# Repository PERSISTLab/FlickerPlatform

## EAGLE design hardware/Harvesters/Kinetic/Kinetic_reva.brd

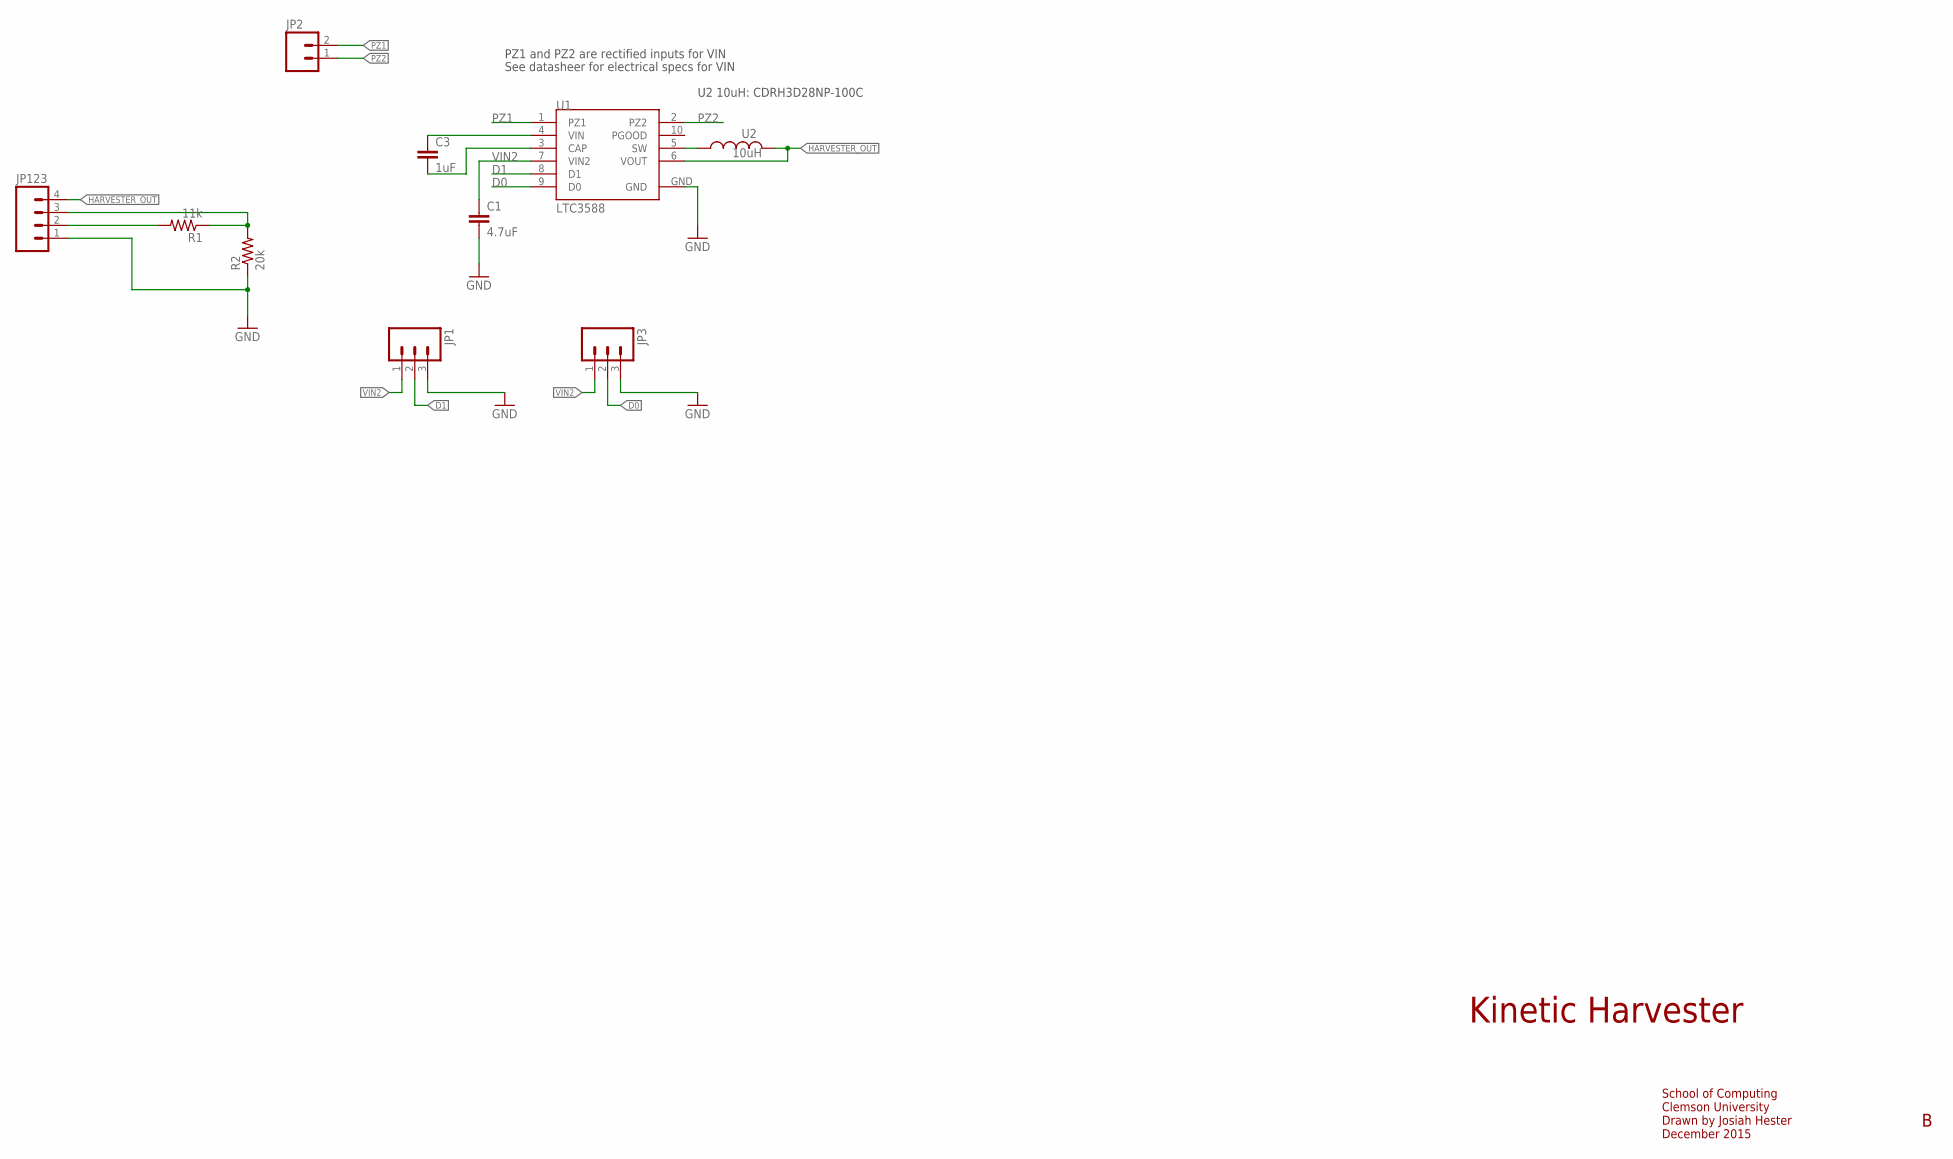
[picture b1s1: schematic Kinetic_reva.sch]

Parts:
C1: 4.7uF; 0402-CAP; MPN C1005X5R1A475M050BC
C3: 1uF; 0402-CAP; MPN 0402ZD105KAT2A
JP1, JP3: M03; 1X03-1.27MM; MPN GRPB031VWVN-RC
JP2: M02LOCK; 1X02_LOCK
JP123: M041.27MM; 1X04-1.27MM; MPN GRPB041VWVN-RC
R1: 11k; 0603; MPN RC0603JR-0711KL
R2: 20k; 0603; MPN CRCW060320K0FKEA
U1: LTC3588; MSOP-10-GNDPAD; MPN LTC3588EMSE-1#PBF; DIGIKEY LTC3588EMSE-1#PBF-ND
U2: 10uH; CDRH3D28; MPN CDRH3D16NP-100NC; DIGIKEY 308-2298-1-ND

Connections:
D0: JP3.2, U1.9 (D0)
D1: JP1.2, U1.8 (D1)
GND: C1.2, JP1.3, JP3.3, JP123.1, R2.1, U1.GND
HARVESTER_OUT: JP123.4, U1.6 (VOUT), U2.2
unnamed: JP123.3, R1.1, R2.2
unnamed: JP123.2, R1.2
unnamed: C3.2, U1.3 (CAP)
unnamed: U1.5 (SW), U2.1
PZ1: JP2.2, U1.1 (PZ1)
PZ2: JP2.1, U1.2 (PZ2)
VIN: C3.1, U1.4 (VIN)
VIN2: C1.1, JP1.1, JP3.1, U1.7 (VIN2)

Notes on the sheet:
Kinetic Harvester
School of Computing Clemson University Drawn by Josiah Hester December 2015
U2 10uH: CDRH3D28NP-100C
PZ1 and PZ2 are rectified inputs for VIN
See datasheer for electrical specs for VIN

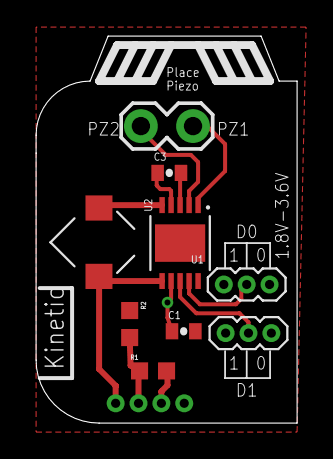
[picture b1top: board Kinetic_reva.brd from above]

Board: 2 copper layers, 14.5 x 21.5 mm, 10 parts (1 on the bottom side), 12 nets.

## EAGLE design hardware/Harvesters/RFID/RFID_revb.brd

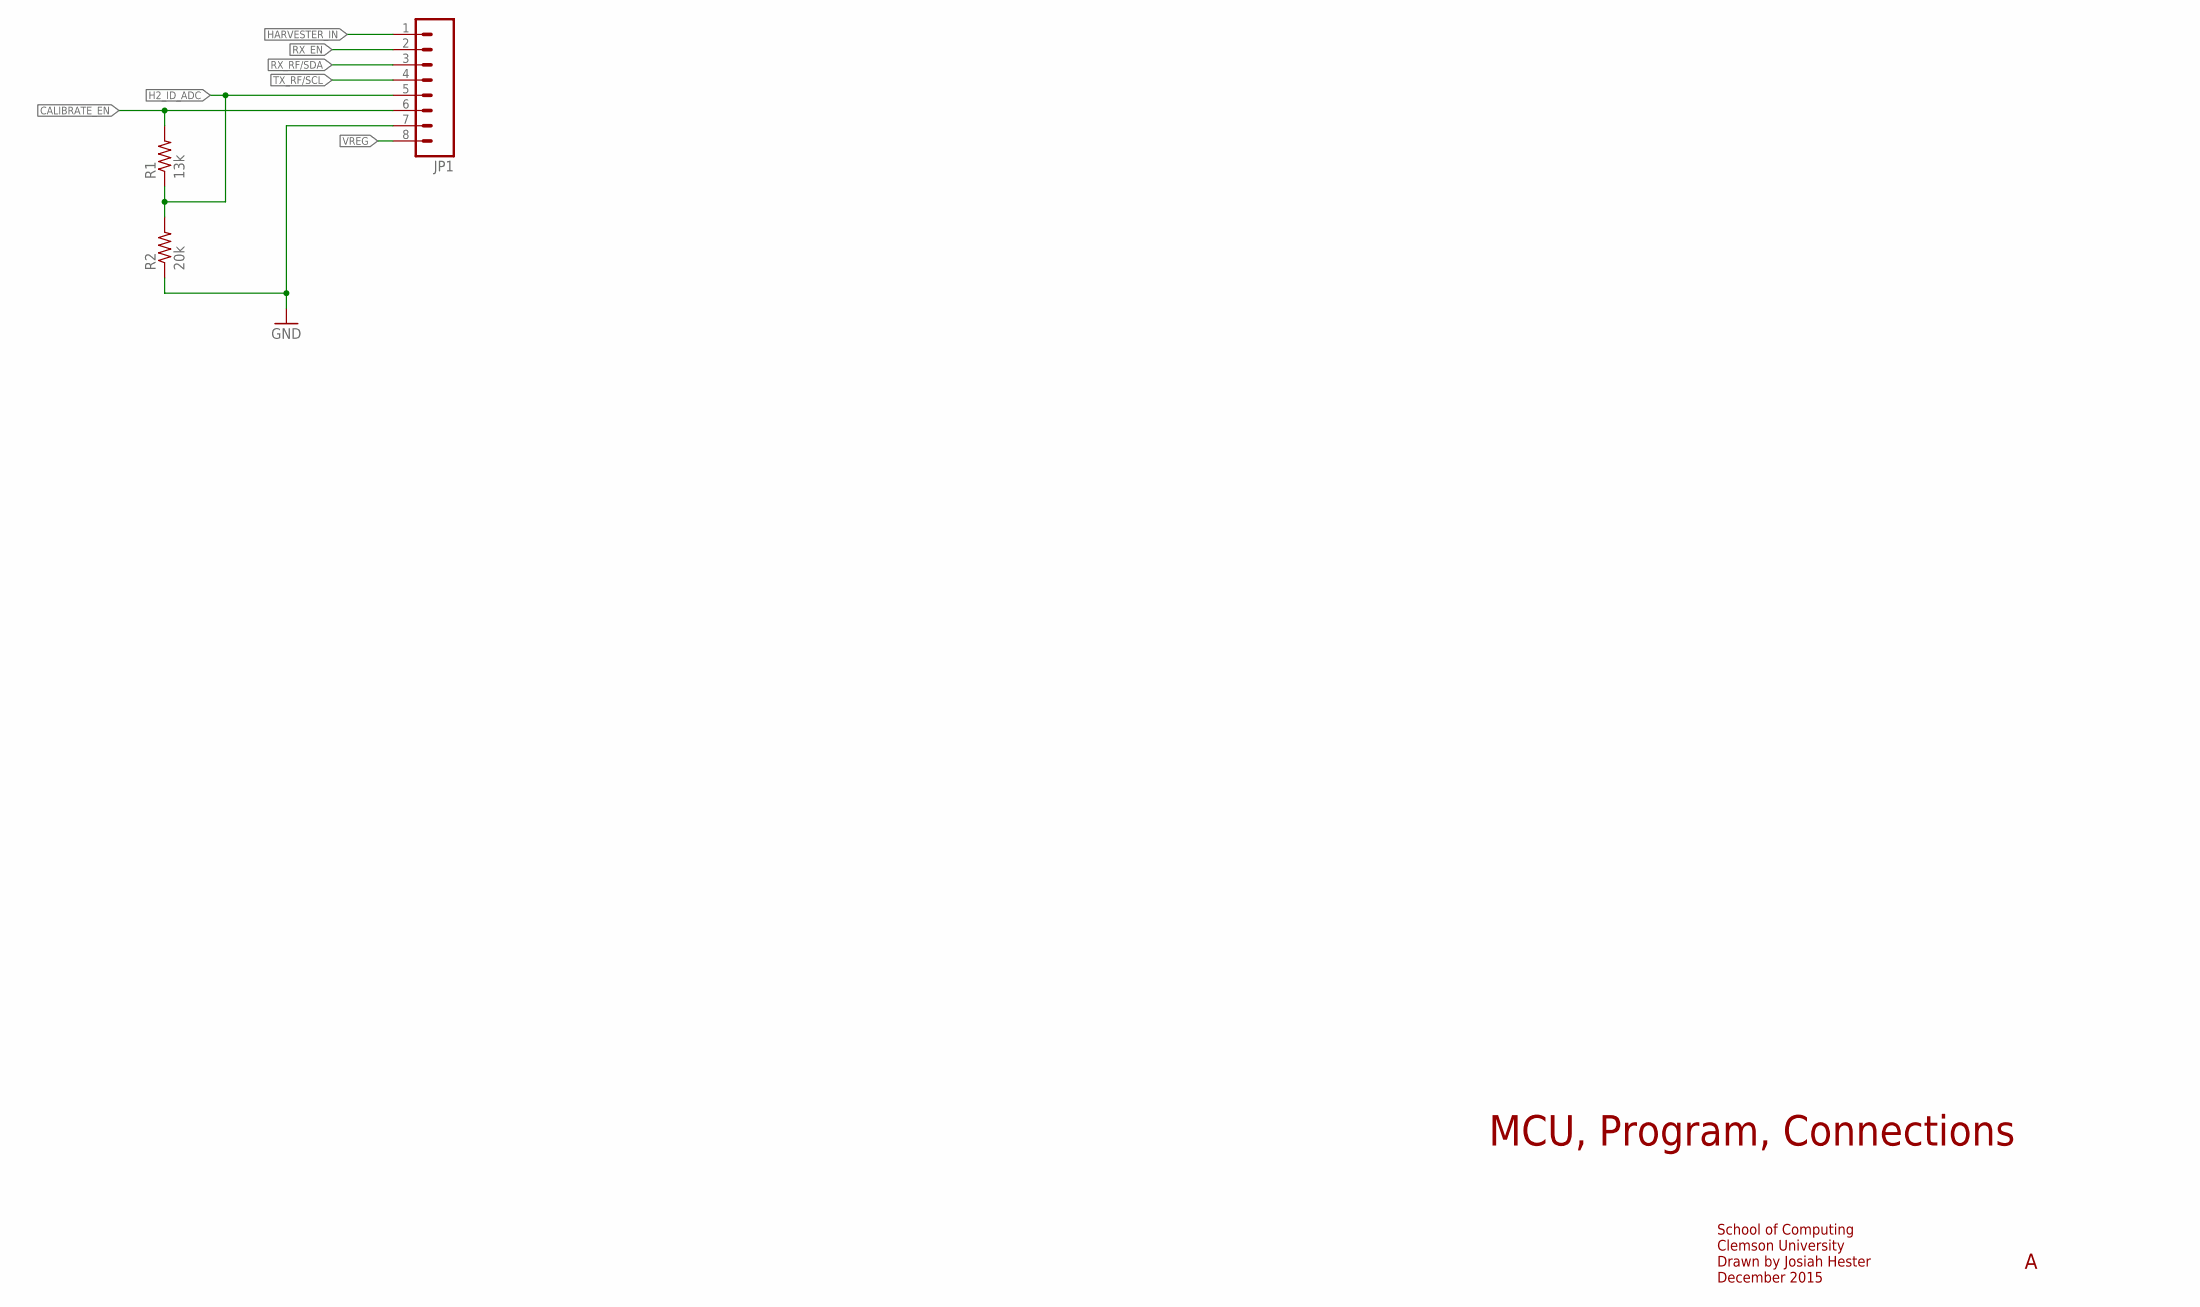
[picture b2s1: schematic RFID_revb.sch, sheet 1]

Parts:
JP1: M081.27MM; 1X08-1.27MM; MPN GRPB081VWVN-RC
R1: 13k; 0603; MPN RC0603FR-0713KL
R2: 20k; 0603; MPN CRCW060320K0FKEA

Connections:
CALIBRATE_EN: JP1.6, R1.2
GND: JP1.7, R2.1; also elsewhere on the board
H2_ID_ADC: JP1.5, R1.1, R2.2
HARVESTER_IN: JP1.1; also elsewhere on the board
RX_EN: JP1.2; also elsewhere on the board
RX_RF/SDA: JP1.3; also elsewhere on the board
TX_RF/SCL: JP1.4; also elsewhere on the board
VREG: JP1.8; also elsewhere on the board

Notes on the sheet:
MCU, Program, Connections
School of Computing Clemson University Drawn by Josiah Hester December 2015

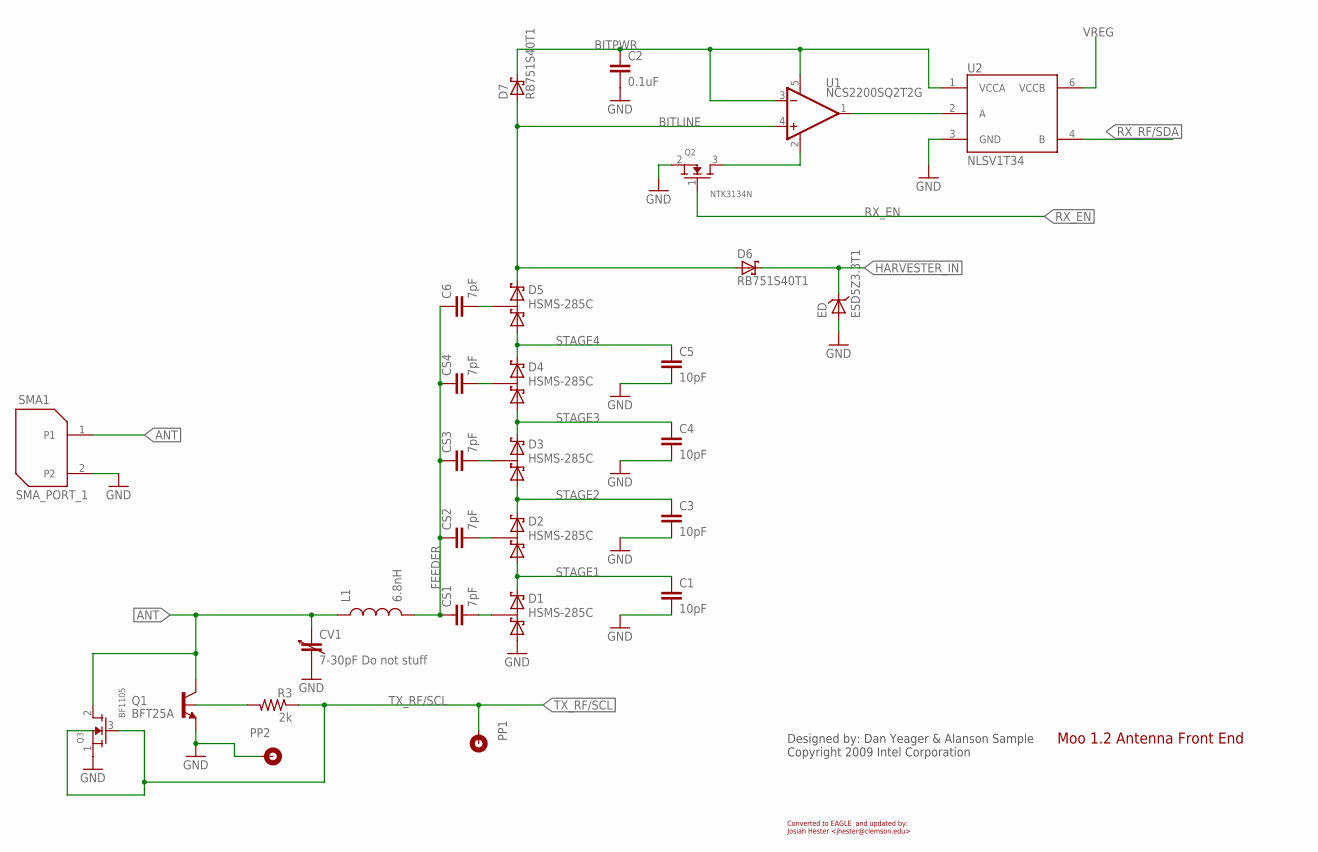
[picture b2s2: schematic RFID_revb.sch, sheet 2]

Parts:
C1, C3, C4, C5: 10pF; 0402; MPN GRM1555C1H100JA01D
C2: 0.1uF; 0402; MPN 0402YD104KAT2A
C6: 7pF; 0402; MPN GRM1555C1H7R0DA01D
CS1, CS2, CS3: 7pF; 0402; MPN GRM1555C1H7R0DA01D; DIGIKEY 490-5878-1-ND
CS4: 7pF; 0402; MPN GRM1555C1H7R0DA01D
CV1: 7-30pF Do not stuff; VAR-CAP_603_1PRIMARY; MPN TZY2R250AC01R00
D1, D2, D3, D4, D5: HSMS-285C; SOT-323,_HSMS-285C_1PRIMARY; MPN HSMS-285C-BLKG
D6, D7: RB751S40T1; SOD-523_1PRIMARY; MPN RB751S40T1G
ED: ESD5Z3.3T1; SOD-523_1PRIMARY; MPN ESD5Z3.3T1G
L1: 6.8nH; 0603_1PRIMARY; MPN MLG1608B6N8DT000
PP1: PROBE_POINT_2; PROBE_POINT_2PRIMARY
PP2: PROBE_POINT_1; PROBE_POINT_2PRIMARY
Q1: BFT25A; SOT-23_1PRIMARY; MPN BFT25A,215; DIGIKEY 568-1992-1-ND
Q2: NTK3134N; SOT723_1PRIMARY; MPN NTK3134NT1G
Q3: BF1105; SOT-143R; MPN BF1105R,215
R3: 2k; 0402; MPN CRCW04022K00FKED
SMA1: SMA_PORT_1; SMA_PORT_1PRIMARY
U1: NCS2200SQ2T2G; SC70-5_1PRIMARY; MPN NCS2200SQ2T2G; DIGIKEY NCS2200SQ2T2GOSCT-ND
U2: NLSV1T34; ULLGA6; MPN NLSV1T34AMX1TCG

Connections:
ANT: CV1.1, L1.1, Q1.3 (C), Q3.2 (D), SMA1.1
BITLINE: D5.2, D6.2 (A), D7.2 (A), U1.4
BITPWR: C2.1, D7.1 (C), U1.3, U1.5, U2.1 (VCCA)
CONTROL: Q1.1 (B), R3.2
FEEDER: C6.1, CS1.1, CS2.1, CS3.1, CS4.1, L1.2
GND: C1.2, C2.2, C3.2, C4.2, C5.2, CV1.2, D1.1, ED.2, PP2.1, Q1.2 (E), Q2.2, Q3.1 (S), SMA1.2, U2.3 (GND); also elsewhere on the board
HARVESTER_IN: D6.1 (C), ED.1; also elsewhere on the board
unnamed: U1.1, U2.2 (A)
unnamed: Q2.3, U1.2
NETCS1_2: CS1.2, D1.3
NETCS2_2: CS2.2, D2.3
NETCS3_2: CS3.2, D3.3
NETCS4_2: CS4.2, D4.3
NETCS5_2: C6.2, D5.3
RX_EN: Q2.1; also elsewhere on the board
RX_RF/SDA: U2.4 (B); also elsewhere on the board
STAGE1: C1.1, D1.2, D2.1
STAGE2: C3.1, D2.2, D3.1
STAGE3: C4.1, D3.2, D4.1
STAGE4: C5.1, D4.2, D5.1
TX_RF/SCL: PP1.1, Q3.3 (G), Q3.4 (G2), R3.1; also elsewhere on the board
VREG: U2.6 (VCCB); also elsewhere on the board

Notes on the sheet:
Designed by: Dan Yeager & Alanson Sample Copyright 2009 Intel Corporation
Moo 1.2 Antenna Front End
Converted to EAGLE and updated by: Josiah Hester <jhester@clemson.edu>

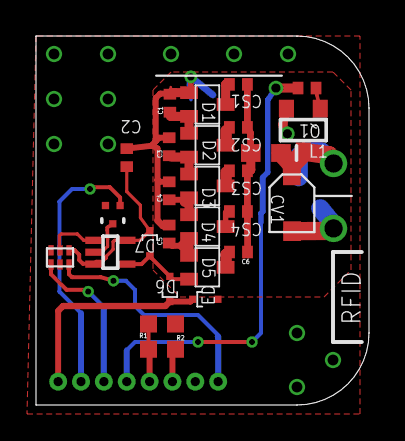
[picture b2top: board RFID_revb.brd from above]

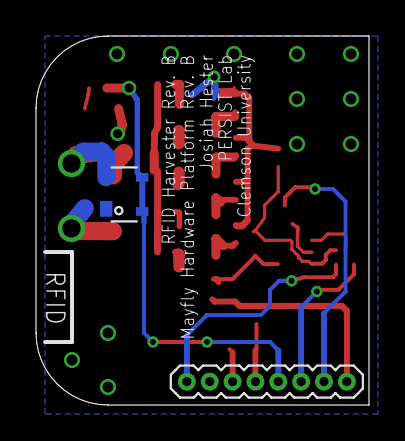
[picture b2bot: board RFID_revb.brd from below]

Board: 2 copper layers, 18.5 x 20.5 mm, 32 parts (2 on the bottom side), 24 nets.

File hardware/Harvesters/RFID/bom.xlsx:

Part | Value | Device | Package | Description | DIGIKEY | MPN
C1 | 10pF | C-EU | 402 |  |  | GRM1555C1H100JA01D
C2 | 0.1uF | C-EU | 402 |  |  | 0402YD104KAT2A
C3 | 10pF | C-EU | 402 |  |  | GRM1555C1H100JA01D
C4 | 10pF | C-EU | 402 |  |  | GRM1555C1H100JA01D
C5 | 10pF | C-EU | 402 |  |  | GRM1555C1H100JA01D
C6 | 7pF | C-EU | 402 |  |  | GRM1555C1H7R0DA01D
CS1 | 7pF | C-EU | 402 |  | 490-5878-1-ND | GRM1555C1H7R0DA01D
CS2 | 7pF | C-EU | 402 |  | 490-5878-1-ND | GRM1555C1H7R0DA01D
CS3 | 7pF | C-EU | 402 |  | 490-5878-1-ND | GRM1555C1H7R0DA01D
CS4 | 7pF | C-EU | 402 |  |  | GRM1555C1H7R0DA01D
CV1 | 7-30pF Do not stuff | VAR-CAP_603_1 | VAR-CAP_603_1PRIMARY |  |  | TZY2R250AC01R00
D1 | HSMS-285C | HSMS-285C | SOT-323,_HSMS-285C_1PRIMARY |  |  | HSMS-285C-BLKG
D2 | HSMS-285C | HSMS-285C | SOT-323,_HSMS-285C_1PRIMARY |  |  | HSMS-285C-BLKG
D3 | HSMS-285C | HSMS-285C | SOT-323,_HSMS-285C_1PRIMARY |  |  | HSMS-285C-BLKG
D4 | HSMS-285C | HSMS-285C | SOT-323,_HSMS-285C_1PRIMARY |  |  | HSMS-285C-BLKG
D5 | HSMS-285C | HSMS-285C | SOT-323,_HSMS-285C_1PRIMARY |  |  | HSMS-285C-BLKG
D6 | RB751S40T1 | RB751S40T1 | SOD-523_1PRIMARY |  |  | RB751S40T1G
D7 | RB751S40T1 | RB751S40T1 | SOD-523_1PRIMARY |  |  | RB751S40T1G
ED | ESD5Z3.3T1 | ESD5Z3.3T1 | SOD-523_1PRIMARY |  |  | ESD5Z3.3T1G
JP1 |  | M081.27MM | 1X08-1.27MM | Header 8 |  | GRPB081VWVN-RC
L1 | 6.8nH | 0603_1 | 0603_1PRIMARY |  |  | MLG1608B6N8DT000
PP1 | PROBE_POINT_2 | PROBE_POINT_2 | PROBE_POINT_2PRIMARY
PP2 | PROBE_POINT_1 | PROBE_POINT_1 | PROBE_POINT_2PRIMARY
Q1 | BFT25A | BFT25A | SOT-23_1PRIMARY |  | 568-1992-1-ND | BFT25A,215
Q2 | NTK3134N | NTK3134N | SOT723_1PRIMARY |  |  | NTK3134NT1G
Q3 | BF1105 | BF1105 | SOT-143R |  |  | BF1105R,215
R1 | 13k | R-EU0603 | 603 |  |  | RC0603FR-0713KL
R2 | 20k | R-EU0603 | 603 |  |  | CRCW060320K0FKEA
R3 | 2k | R-EU | 402 |  |  | CRCW04022K00FKED
SMA1 | SMA_PORT_1 | SMA_PORT_1 | SMA_PORT_1PRIMARY
U1 | NCS2200SQ2T2G | NCS2200SQ2T2G | SC70-5_1PRIMARY |  |  | 0402YD104KAT2A
U2 | NLSV1T34 | NLSV1T34 | ULLGA6 |  |  | NLSV1T34AMX1TCG

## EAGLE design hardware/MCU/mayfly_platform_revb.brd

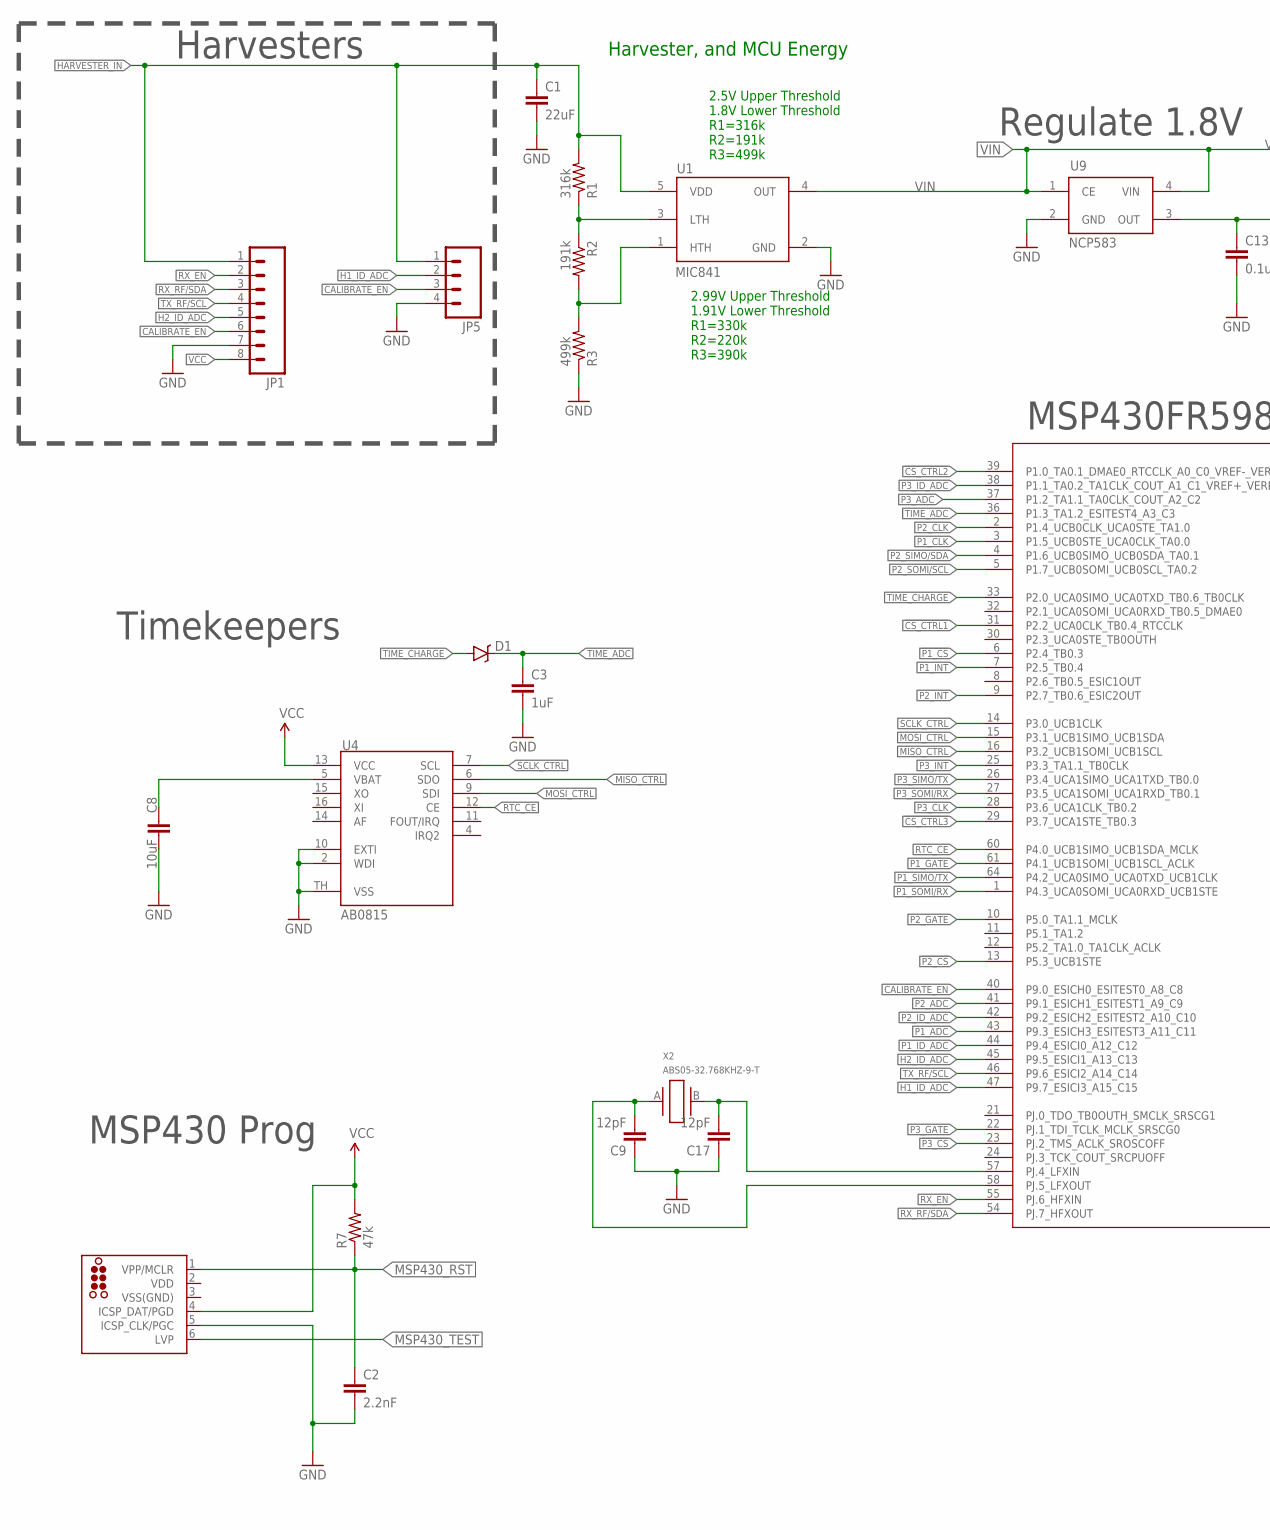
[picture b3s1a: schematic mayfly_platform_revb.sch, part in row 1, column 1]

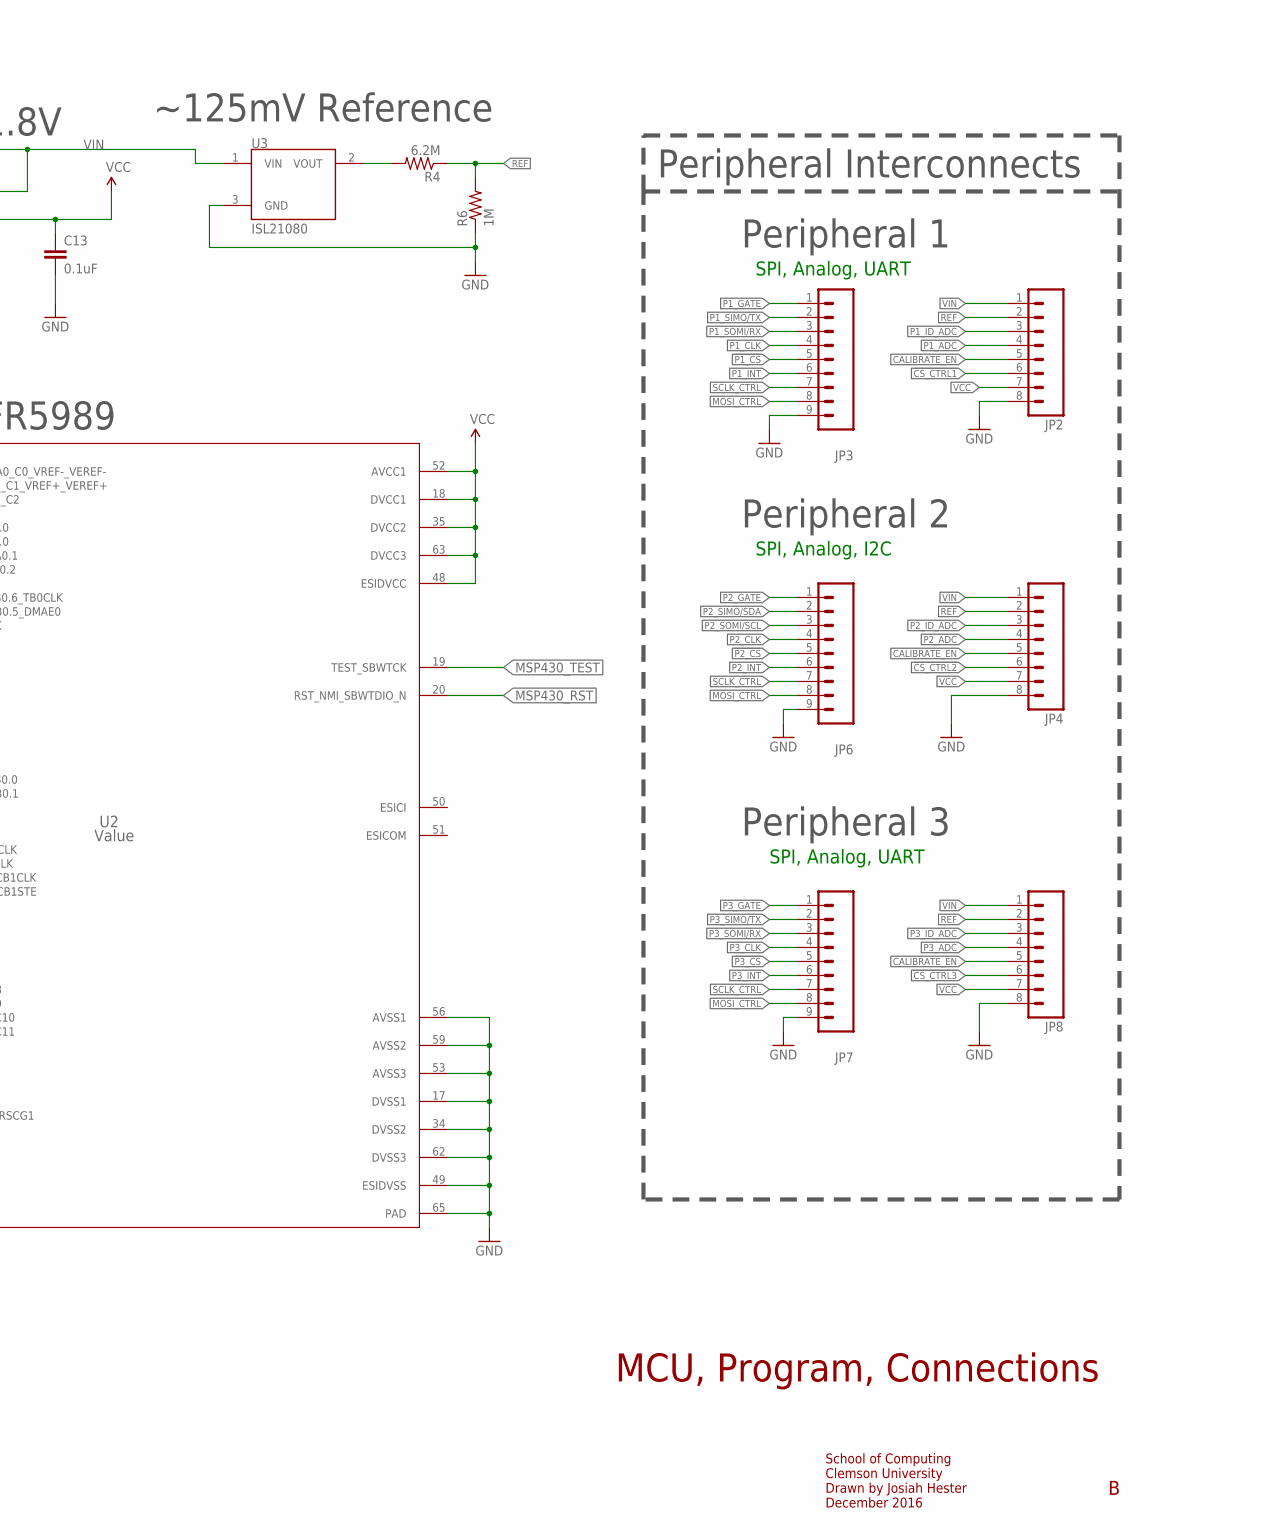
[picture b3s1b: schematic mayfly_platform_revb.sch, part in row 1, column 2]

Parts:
C1: 22uF; 1210; MANUFACTURERPARTNUMBER CL32A226KAJNNNE
C2: 2.2nF; 0603; MPN 06035C222KAT2A
C3: 1uF; 0603; MANUFACTURERPARTNUMBER 0603YD105KAT2A
C8: 10uF; 0805; MPN 0805YD106KAT2A
C9, C17: 12pF; 0603; MPN CL10C120JB8NNNC
C13: 0.1uF; 0603; MANUFACTURERPARTNUMBER 0603YC104KAT2A
D1: RB751; SOD-523; MPN BAS40-02V-V-G-08; DIGIKEY BAS40-02V-V-G-08GICT-ND
J1: TC2030-MCP-NL
JP1: M081.27MM; 1X08-1.27MM; MANUFACTURERPARTNUMBER 851-43-008-10-001000; DIGIKEY ED90570-ND
JP2, JP4, JP8: M081.27MM; 1X08-1.27MM; MPN 851-43-008-10-001000; DIGIKEY ED90570-ND
JP3, JP6, JP7: M091.27MM; 1X09-1.27MM; MPN 851-87-009-10-001101; DIGIKEY 1212-1354-ND
JP5: M041.27MM; 1X04-1.27MM; MANUFACTURERPARTNUMBER 851-43-004-10-001000; DIGIKEY ED90528-ND
R1: 316k; 0603; MANUFACTURERPARTNUMBER RC0603FR-07316KL; DIGIKEY 311-316KHRCT-ND
R2: 191k; 0603; MANUFACTURERPARTNUMBER RC0603FR-07191KL; DIGIKEY 311-191KHRCT-ND
R3: 499k; 0603; MANUFACTURERPARTNUMBER RC0603FR-07499KL; DIGIKEY 311-499KHRCT-ND
R4: 6.2M; 0603; MPN CRCW06036M20FKEA; DIGIKEY 541-6.20MHCT-ND
R6: 1M; 0603; MPN RC0603FR-071ML; DIGIKEY 311-1.00MHRCT-ND
R7: 47k; 0603; MPN CRCW060347K0JNEA
U1: MIC841; SC70-5; MPN MIC841HYC5-TR; DIGIKEY 576-2923-1-ND
U2: Value; RGC0064B; MPN MSP430FR59891IRGCT; DIGIKEY 296-42031-1-ND
U3: ISL21080; SOT-23; MPN ISL21080DIH309Z-TK; DIGIKEY ISL21080DIH309Z-TKCT-ND
U4: AB0815; QFN16; MPN AB0815-T3
U9: NCP583; SC82-AB_1PRIMARY; MPN NCP583SQ18T1G; DIGIKEY NCP583SQ18T1GOSCT-ND
X2: ABS05-32.768KHZ-9-T; ABS05; MPN ABS05-32.768KHZ-9-T

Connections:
!CS_CTRL1: JP2.6, U2.31 (P2.2_UCA0CLK_TB0.4_RTCCLK)
!CS_CTRL2: JP4.6, U2.39 (P1.0_TA0.1_DMAE0_RTCCLK_A0_C0_VREF-_VER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)
!CS_CTRL3: JP8.6, U2.29 (P3.7_UCA1STE_TB0.3)
!P1_CS: JP3.5, U2.6 (P2.4_TB0.3)
!P2_CS: JP6.5, U2.13 (P5.3_UCB1STE)
!P3_CS: JP7.5, U2.23 (PJ.2_TMS_ACLK_SROSCOFF)
CALIBRATE_EN: JP1.6, JP2.5, JP4.5, JP5.3, JP8.5, U2.40 (P9.0_ESICH0_ESITEST0_A8_C8)
GND: C1.2, C2.2, C3.2, C8.2, C9.1, C13.2, C17.1, J1.5 (ICSP_CLK/PGC), JP1.7, JP2.8, JP3.9, JP4.8, JP5.4, JP6.9, JP7.9, JP8.8, R3.1, R6.1, U1.2 (GND), U2.17 (DVSS1), U2.34 (DVSS2), U2.49 (ESIDVSS), U2.53 (AVSS3), U2.56 (AVSS1), U2.59 (AVSS2), U2.62 (DVSS3), U2.65 (PAD), U3.3 (GND), U4.2 (WDI), U4.10 (EXTI), U4.TH (VSS), U9.2 (GND)
H1_ID_ADC: JP5.2, U2.47 (P9.7_ESICI3_A15_C15)
H2_ID_ADC: JP1.5, U2.45 (P9.5_ESICI1_A13_C13)
HARVESTER_IN: C1.1, JP1.1, JP5.1, R1.2, U1.5 (VDD)
MISO_CTRL: U2.16 (P3.2_UCB1SOMI_UCB1SCL), U4.6 (SDO)
MOSI_CTRL: JP3.8, JP6.8, JP7.8, U2.15 (P3.1_UCB1SIMO_UCB1SDA), U4.9 (SDI)
MSP430_RST: C2.1, J1.1 (VPP/MCLR), R7.1, U2.20 (RST_NMI_SBWTDIO_N)
MSP430_TEST: J1.6 (LVP), U2.19 (TEST_SBWTCK)
unnamed: R1.1, R2.1, U1.3 (LTH)
unnamed: R4.2, U3.2 (VOUT)
unnamed: R2.2, R3.2, U1.1 (HTH)
unnamed: C17.2, U2.57 (PJ.4_LFXIN), X2.B (2)
unnamed: C9.2, U2.58 (PJ.5_LFXOUT), X2.A (1)
unnamed: C8.1, U4.5 (VBAT)
P1_ADC: JP2.4, U2.43 (P9.3_ESICH3_ESITEST3_A11_C11)
P1_CLK: JP3.4, U2.3 (P1.5_UCB0STE_UCA0CLK_TA0.0)
P1_GATE: JP3.1, U2.61 (P4.1_UCB1SOMI_UCB1SCL_ACLK)
P1_ID_ADC: JP2.3, U2.44 (P9.4_ESICI0_A12_C12)
P1_INT: JP3.6, U2.7 (P2.5_TB0.4)
P1_SIMO/TX: JP3.2, U2.64 (P4.2_UCA0SIMO_UCA0TXD_UCB1CLK)
P1_SOMI/RX: JP3.3, U2.1 (P4.3_UCA0SOMI_UCA0RXD_UCB1STE)
P2_ADC: JP4.4, U2.41 (P9.1_ESICH1_ESITEST1_A9_C9)
P2_CLK: JP6.4, U2.2 (P1.4_UCB0CLK_UCA0STE_TA1.0)
P2_GATE: JP6.1, U2.10 (P5.0_TA1.1_MCLK)
P2_ID_ADC: JP4.3, U2.42 (P9.2_ESICH2_ESITEST2_A10_C10)
P2_INT: JP6.6, U2.9 (P2.7_TB0.6_ESIC2OUT)
P2_SIMO/SDA: JP6.2, U2.4 (P1.6_UCB0SIMO_UCB0SDA_TA0.1)
P2_SOMI/SCL: JP6.3, U2.5 (P1.7_UCB0SOMI_UCB0SCL_TA0.2)
P3_ADC: JP8.4, U2.37 (P1.2_TA1.1_TA0CLK_COUT_A2_C2)
P3_CLK: JP7.4, U2.28 (P3.6_UCA1CLK_TB0.2)
P3_GATE: JP7.1, U2.22 (PJ.1_TDI_TCLK_MCLK_SRSCG0)
P3_ID_ADC: JP8.3, U2.38 (P1.1_TA0.2_TA1CLK_COUT_A1_C1_VREF+_VERE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)
P3_INT: JP7.6, U2.25 (P3.3_TA1.1_TB0CLK)
P3_SIMO/TX: JP7.2, U2.26 (P3.4_UCA1SIMO_UCA1TXD_TB0.0)
P3_SOMI/RX: JP7.3, U2.27 (P3.5_UCA1SOMI_UCA1RXD_TB0.1)
REF: JP2.2, JP4.2, JP8.2, R4.1, R6.2
RTC_CE: U2.60 (P4.0_UCB1SIMO_UCB1SDA_MCLK), U4.12 (CE)
RX_EN: JP1.2, U2.55 (PJ.6_HFXIN)
RX_RF/SDA: JP1.3, U2.54 (PJ.7_HFXOUT)
SCLK_CTRL: JP3.7, JP6.7, JP7.7, U2.14 (P3.0_UCB1CLK), U4.7 (SCL)
TIME_ADC: C3.1, D1.C, U2.36 (P1.3_TA1.2_ESITEST4_A3_C3)
TIME_CHARGE: D1.A, U2.33 (P2.0_UCA0SIMO_UCA0TXD_TB0.6_TB0CLK)
TX_RF/SCL: JP1.4, U2.46 (P9.6_ESICI2_A14_C14)
VCC: C13.1, J1.4 (ICSP_DAT/PGD), JP1.8, JP2.7, JP4.7, JP8.7, R7.2, U2.18 (DVCC1), U2.35 (DVCC2), U2.48 (ESIDVCC), U2.52 (AVCC1), U2.63 (DVCC3), U4.13 (VCC), U9.3 (OUT)
VDD: J1.2 (VDD)
VIN: JP2.1, JP4.1, JP8.1, U1.4 (OUT), U3.1 (VIN), U9.1 (CE), U9.4 (VIN)
VSS(GND): J1.3 (VSS(GND))

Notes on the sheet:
MCU, Program, Connections
School of Computing Clemson University Drawn by Josiah Hester December 2016
MSP430FR5989
Regulate 1.8V
MSP430 Prog
Timekeepers
2.99V Upper Threshold 1.91V Lower Threshold R1=330k R2=220k R3=390k
Harvester, and MCU Energy
~125mV Reference
Peripheral 1
Peripheral 2
Peripheral 3
Harvesters
SPI, Analog, I2C
SPI, Analog, UART
Peripheral Interconnects
2.5V Upper Threshold 1.8V Lower Threshold R1=316k R2=191k R3=499k

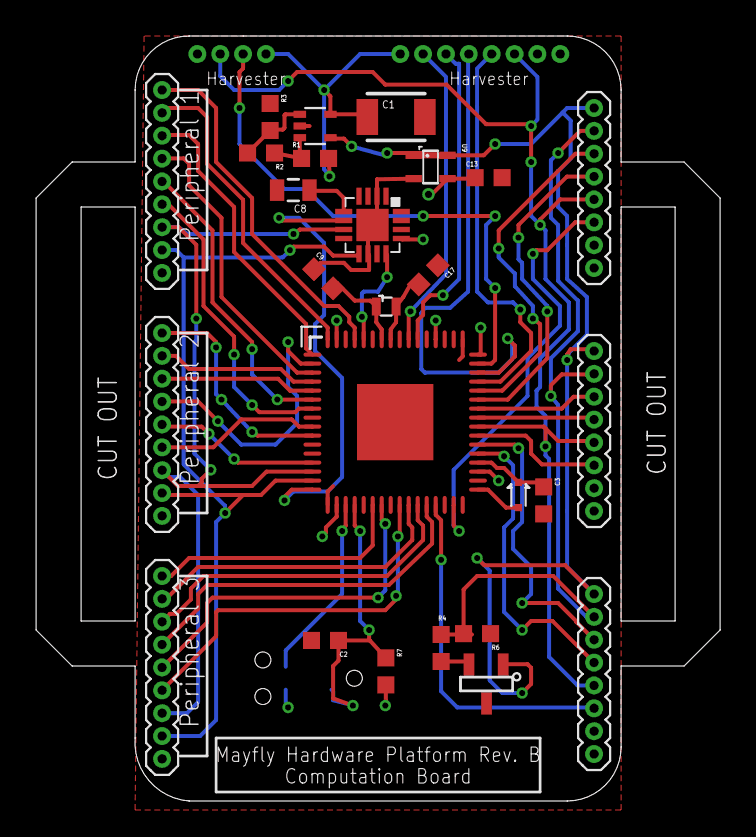
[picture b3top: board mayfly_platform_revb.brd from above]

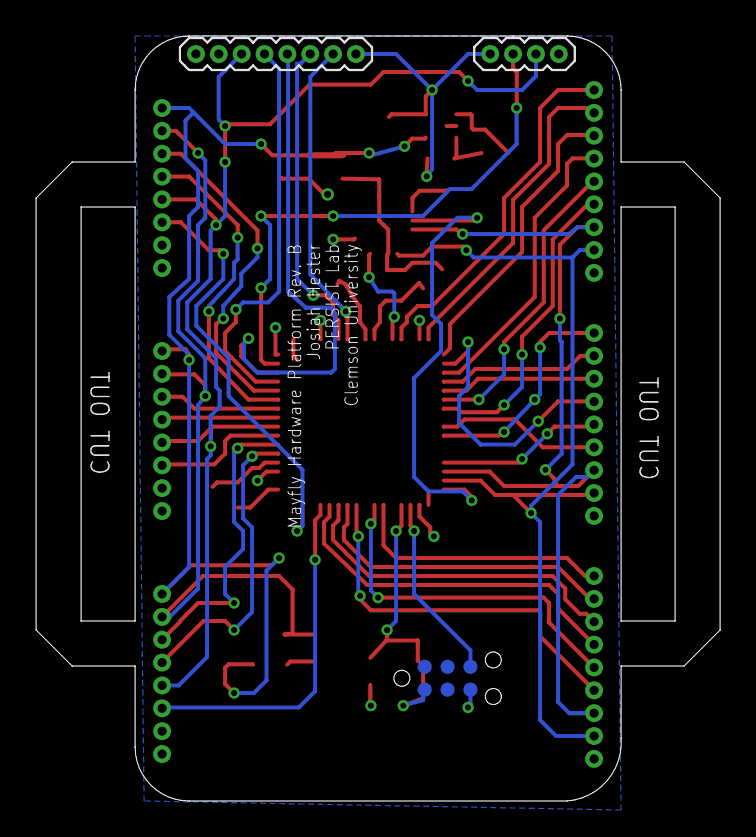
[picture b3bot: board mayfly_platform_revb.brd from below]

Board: 2 copper layers, 38.0 x 42.5 mm, 29 parts (3 on the bottom side), 52 nets.

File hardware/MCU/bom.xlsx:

Part | Value | Device | Package | Description | ALTERNATEPARTNUMBER | COMPTYPE | DIGIKEY | MANUFACTURER | MANUFACTURERPARTNUMBER | MOUNTTYPE | MPN | PACKAGEREFERENCE | PARTNUMBER | PIN_COUNT | PROD_ID | REFDES | ROHS | TYPE | VALUE
C1 | 22uF | CAP1210 | 1210 | Capacitor
C2 | 2.2nF | C-EU0603 | 603 |  |  |  |  |  |  |  | 06035C222KAT2A
C3 | 1uF | C-EU0603 | 603 |  |  |  |  |  | 0603YD105KAT2A |  | 0603YD105KAT2A
C8 | 10uF | CAP0805 | 805 | Capacitor |  |  |  |  |  |  | 0805YD106KAT2A
C9 | 12pF | C-EU0603 | 603 |  |  |  |  |  |  |  | CL10C120JB8NNNC
C13 | 0.1uF | C-EU0603 | 603 |  |  |  |  |  | 0603YC104KAT2A |  | 0603YC104KAT2A
C17 | 12pF | C-EU0603 | 603 |  |  |  |  |  |  |  | CL10C120JB8NNNC
D1 | RB751 | DIODE-SCHOTTKY-RB751 | SOD-523 | Schottky diodes in SFE's production catalog |  |  | BAS40-02V-V-G-08GICT-ND |  |  |  | BAS40-02V-V-G-08
J1 |  | TC2030-MCP-NL | TC2030-MCP-NL | TAG-CONNECT ICSP ConnectorManufacturer: Tag-Connect
JP1 |  | M081.27MM | 1X08-1.27MM | Header 8 |  |  | ED90570-ND |  | 851-43-008-10-001000 |  | 851-43-008-10-001000
JP2 |  | M081.27MM | 1X08-1.27MM | Header 8 |  |  | ED90570-ND |  |  |  | 851-43-008-10-001000
JP3 |  | M091.27MM | 1X09-1.27MM | Header 9 |  |  | 1212-1354-ND |  |  |  | 851-87-009-10-001101
JP4 |  | M081.27MM | 1X08-1.27MM | Header 8 |  |  | ED90570-ND |  |  |  | 851-43-008-10-001000
JP5 |  | M041.27MM | 1X04-1.27MM | Header 4 |  |  | ED90528-ND |  | 851-43-004-10-001000 |  | 851-43-004-10-001000
JP6 |  | M091.27MM | 1X09-1.27MM | Header 9 |  |  | 1212-1354-ND |  |  |  | 851-87-009-10-001101
JP7 |  | M091.27MM | 1X09-1.27MM | Header 9 |  |  | 1212-1354-ND |  |  |  | 851-87-009-10-001101
JP8 |  | M081.27MM | 1X08-1.27MM | Header 8 |  |  | ED90570-ND |  |  |  | 851-43-008-10-001000
R1 | 316k | R-EU0603 | 603 |  |  |  | 311-316KHRCT-ND |  | RC0603FR-07316KL |  | RC0603FR-07316KL
R2 | 191k | R-EU0603 | 603 |  |  |  | 311-191KHRCT-ND |  | RC0603FR-07191KL |  | RC0603FR-07191KL
R3 | 499k | R-EU0603 | 603 |  |  |  | 311-499KHRCT-ND |  | RC0603FR-07499KL |  | RC0603FR-07499KL
R4 | 6.2M | R-EU0603 | 603 |  |  |  | 541-6.20MHCT-ND |  |  |  | CRCW06036M20FKEA
R6 | 1M | R-EU0603 | 603 |  |  |  | 311-1.00MHRCT-ND |  |  |  | RC0603FR-071ML
R7 | 47k | R-EU0603 | 603 |  |  |  |  |  |  |  | CRCW060347K0JNEA
U1 | MIC841 | MIC841 | SC70-5 | MIC841:Comparator with reference and adj. hysteresis |  |  | 576-2923-1-ND |  |  |  | MIC841HYC5-TR
U2 | Value | MSP430FR5989IRGCR | RGC0064B |  | MSP430FR5989IRGCT | IC | 296-42031-1-ND | Texas Instruments |  | SMT | MSP430FR59891IRGCT | RGC0064B | MSP430FR5989IRGCR | 65 |  | RefDes | Y | TYPE | Value
U3 | ISL21080 | ISL21080 | SOT-23 | Intersil: ISL21080, 300nA NanoPower Voltage References |  |  | ISL21080DIH309Z-TKCT-ND |  |  |  | ISL21080DIH309Z-TK
U4 | AB0815 | AB0815 | QFN16 | AB08X5 Real-Time Clock Family: SPI |  |  | 535-11930-1-ND |  |  |  | AB0815-T3
U9 | NCP583 | NCP583 | SC82-AB_1PRIMARY | NCP583 - Ultra-Low Iq 150 mA CMOS LDO Regulator with Enable |  |  | NCP583SQ18T1GOSCT-ND |  |  |  | NCP583SQ18T1G
X2 | ABS05-32.768KHZ-9-T | ABS05-32.768KHZ-9-T | ABS05 | 32.768kHz Crystal |  |  | 535-11897-1-ND |  |  |  | ABS05-32.768KHZ-9-T

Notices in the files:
parts and their libraries:
SparkFun-Connectors: Licensing: Creative Commons ShareAlike 4.0 International - https://creativecommons.org/licenses/by-sa/4.0
tag-connect_msp430: ©2009 ROFA.cz - modified and updated by Robert Darlington ‹rdarlington@gmail.com›
